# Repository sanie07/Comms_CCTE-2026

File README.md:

# Comms_CCTE-2026
Sistema de comunicación para el cohete suborbital URUTAU-III.

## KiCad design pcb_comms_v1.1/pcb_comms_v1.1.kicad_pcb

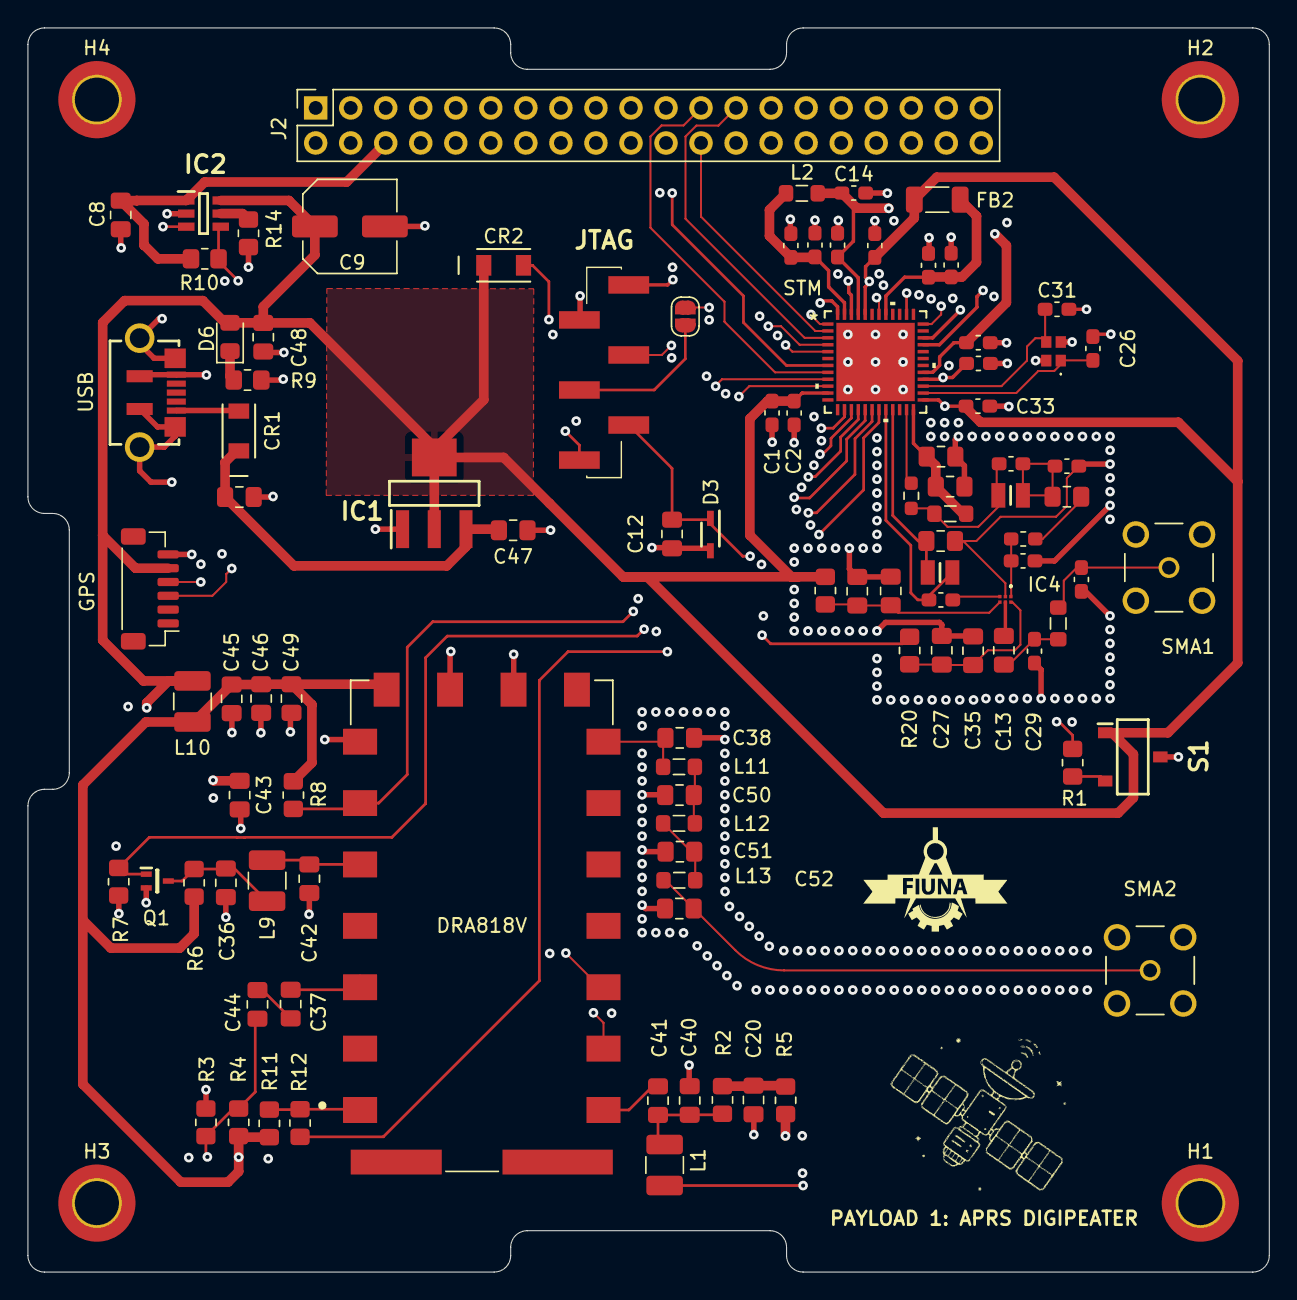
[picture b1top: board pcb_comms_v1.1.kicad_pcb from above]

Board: 4 copper layers, 90.0 x 90.2 mm, 102 parts (0 on the bottom side), 63 nets.

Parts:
C1, C6, C10: 4.7uF; C_0603_1608Metric_Pad1.08x0.95mm_HandSolder
C2, C3, C7, C11, C16: 0.1uF; C_0603_1608Metric_Pad1.08x0.95mm_HandSolder
C8, C39, C46, C49: 10uF; C_0805_2012Metric_Pad1.18x1.45mm_HandSolder
C9: 150uF; C_Elec_6.3x7.7
C12, C43: 0.1uF; C_0805_2012Metric_Pad1.18x1.45mm_HandSolder
C13, C18, C19: 68pF; C_0805_2012Metric_Pad1.18x1.45mm_HandSolder
C14: 0.47uF; C_0603_1608Metric_Pad1.08x0.95mm_HandSolder
C15: 47nF; C_0805_2012Metric_Pad1.18x1.45mm_HandSolder
C17: 2.7pF; C_0603_1608Metric_Pad1.08x0.95mm_HandSolder
C20, C44, C47: 1uF; C_0805_2012Metric_Pad1.18x1.45mm_HandSolder
C21: 15pF; C_0603_1608Metric_Pad1.08x0.95mm_HandSolder
C22: 5.6pF; C_0603_1608Metric_Pad1.08x0.95mm_HandSolder
C23, C27: 10pF; C_0805_2012Metric_Pad1.18x1.45mm_HandSolder
C24: 3.6pF; C_0603_1608Metric_Pad1.08x0.95mm_HandSolder
C25, C35, C36, C42, C45: 1nF; C_0805_2012Metric_Pad1.18x1.45mm_HandSolder
C26, C31: 6.8pF; C_0603_1608Metric_Pad1.08x0.95mm_HandSolder
C28, C29: 8.2pF; C_0603_1608Metric_Pad1.08x0.95mm_HandSolder
C30: 4.3pF; C_0805_2012Metric_Pad1.18x1.45mm_HandSolder
C32, C33, C34: 33pF; C_0603_1608Metric_Pad1.08x0.95mm_HandSolder
C37, C41: 220nF; C_0805_2012Metric_Pad1.18x1.45mm_HandSolder
C38, C52: 20pF; C_0805_2012Metric_Pad1.18x1.45mm_HandSolder
C40: 220pF; C_0805_2012Metric_Pad1.18x1.45mm_HandSolder
C48: 4.7uF; C_0805_2012Metric_Pad1.18x1.45mm_HandSolder
C50, C51: 36pF; C_0805_2012Metric_Pad1.18x1.45mm_HandSolder
CR1, CR2: SD1206S040S1R0; SCHOTTKY_DIODE_SD1206S040S1R0
D3: AQ3530-01FTG; ESD_PROTECTION_DIODE_AQ3530-01FTG
D6: GREEN; LED_0805_2012Metric_Pad1.15x1.40mm_HandSolder
DRA818V: DRA818V; DORJI_DRA818V
FB2: 600R; L_1206_3216Metric_Pad1.22x1.90mm_HandSolder
GPS: CONN_GPS; JST_SH_BM06B-SRSS-TB_1x06-1MP_P1.00mm_Vertical
H1, H2, H3, H4: MountingHole; MountingHole_3.2mm_M3_DIN965_Pad_TopBottom
IC1: LDL1117S33R; LDO_LDL1117S33R
IC2: TPS2553QDBVRQ1; SOT95P280X145-6N
IC4: BGS12WN6E6329XTSA1
J2: Conn_02x20_Odd_Even; PinSocket_2x20_P2.54mm_Vertical
JTAG: Conn_01x06_Pin; CONN_01x06_87898-0666
L1, L9, L10: 1uH; L_1210_3225Metric_Pad1.42x2.65mm_HandSolder
L2: 15uH; L_0805_2012Metric_Pad1.05x1.20mm_HandSolder
L3, L11, L13: 56nH; L_0805_2012Metric_Pad1.05x1.20mm_HandSolder
L4: 12nH; Inductor_0805_2015metric
L5: 20nH; L_0603_1608Metric_Pad1.05x0.95mm_HandSolder
L6: 0R; R_0603_1608Metric_Pad0.98x0.95mm_HandSolder
L7: 18nH; L_0805_2012Metric_Pad1.05x1.20mm_HandSolder
L8: 36nH; Inductor_0805_2015metric
L12: 68nH; L_0805_2012Metric_Pad1.05x1.20mm_HandSolder
Q1: DTC144EET1G; TRANSISTOR_DTC144EET1G
R1, R2, R3, R4, R6, R7, R8, R10, R11: 10K; R_0805_2012Metric_Pad1.20x1.40mm_HandSolder
R5, R9: 1K; R_0805_2012Metric_Pad1.20x1.40mm_HandSolder
R12, R19, R20: 100R; R_0805_2012Metric_Pad1.20x1.40mm_HandSolder
R14: 26.1K; R_0805_2012Metric_Pad1.20x1.40mm_HandSolder
S1: CJS-1200B1; SW_BOOT_CJS-1200B1
SB3: Open; SolderJumper-2_P1.3mm_Open_RoundedPad1.0x1.5mm
SMA1, SMA2: SMA_CONNECTOR; LPRS_SMA_CONNECTOR
STM: STM32WLE5CCU6; UFQFPN48_STM
USB: USB-B-Micro; USB_RECEPTACLE_105164-0001
Y3: 32MHz; STM32WLE5_Crystal_32MHz_ECS320837CKMTR3

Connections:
+3V3: C1.2, C2.2, C3.2, C9.1, C32.1, C33.1, C43.1, C48.1, CR2.1, D6.2 (A), FB2.1, GPS.5, IC1.2 (VOUT_1), IC1.4 (VOUT_2), IC2.6 (OUT), L10.1, R19.2, S1.1, STM.11 (VDD), STM.25 (VDDPA), STM.28 (VDDRF), STM.44 (VDD), STM.46 (VDDSMPS)
+5V: C39.1, C47.1, CR1.1, IC1.3 (VIN)
/APRS_RADIO/3V3_DRA: C45.1, C46.1, C49.1, DRA818V.8 (VBAT), L10.2, R4.2, R5.2, R6.2, R8.2, R11.2
/APRS_RADIO/3V3_DRA1: C20.1, R2.2, R5.1
/APRS_RADIO/AF_OUT: C37.1, DRA818V.3 (AF_OUT)
/APRS_RADIO/AF_OUT2: C37.2, C44.2
/APRS_RADIO/ANT1: C50.1, L11.2, L12.1
/APRS_RADIO/ANT2: C51.1, L12.2, L13.1
/APRS_RADIO/DRA_ANT: C52.1, L13.2, SMA2.1
/APRS_RADIO/DRA_ANT_NO_FILTER: C38.1, DRA818V.12 (ANT), L11.1
/APRS_RADIO/DRA_PTT: C42.1, DRA818V.5 (PTT), L9.2
/APRS_RADIO/DRA_PTT2: C36.1, L9.1, Q1.3 (C), R6.1
/APRS_RADIO/MIC_IN: C41.2, DRA818V.18 (MIC_IN)
/APRS_RADIO/MIC_IN1: C40.1, C41.1, L1.2, R2.1
/IO_CONN/VBUS: CR1.2, USB.1 (VBUS)
/MCU/STM32_BOOT: R1.1, STM.19 (PH3-BOOT0)
/MCU/STM32_OSC_IN: C26.2, STM.26 (OSC_IN), Y3.1 (IN/OUT)
/MCU/STM32_OSC_OUT: C31.2, STM.27 (OSC_OUT), Y3.3 (OUT/IN)
/MCU/VDDA: C6.1, C7.1, FB2.2, STM.41 (VDDA)
/MCU/VDDRF1V55: C14.1, C16.1, C34.1, L2.2, STM.29 (VDDRF1V55), STM.45 (VFBSMPS)
/MCU/VLXSMPS: C10.1, C11.1, L2.1, STM.47 (VLXSMPS)
/OCP/D6_TO_R9: D6.1 (K), R9.2
/OCP/ILIM: IC2.5 (ILIM), R14.1
/RF/RF1: C24.2, IC4.3 (RF1)
/RF/RF2: C22.1, IC4.1 (RF2), L5.2
/RF/RFIN: C13.2, IC4.5 (RFIN)
/RF/RFIN2: C13.1, C29.2, L7.2
/RF/RFO_TO_CAP: C17.1, L3.2, L4.1, L6.2
/RF/RF_C19_TO_L5: C19.2, L5.1
/RF/RF_NODO1: C17.2, C19.1, C21.1, L4.2
/RF/SMA1: C28.2, L7.1, SMA1.1
/RF/SWITCH_TO_CRL: C27.1, C35.1, IC4.6 (CTRL), R20.1
/RF/VDD_SWITCH_RF: C23.1, C25.1, IC4.4 (VDD), R19.1
DRA_RX_UART1_TX: DRA818V.16 (RXD), STM.4 (PB6)
DRA_SQ_TO_STM32: R12.1, STM.16 (PA8)
DRA_TO_STM32_ADC: C44.1, R3.1, R4.1, STM.34 (PA11)
DRA_TX_UART1_RX: DRA818V.17 (TXD), STM.5 (PB7)
GND: C1.1, C2.1, C3.1, C6.2, C7.2, C8.2, C9.2, C10.2, C11.2, C12.2, C14.2, C15.2, C16.2, C18.2, C20.2, C21.2, C22.2, C23.2, C25.2, C26.1, C27.2, C28.1, C29.1, C30.2, C31.1, C32.2, C33.2, C34.2, C35.2, C36.2, C38.2, C39.2, C40.2, C42.2, C43.2, C45.2, C46.2, C47.2, C48.2, C49.2, C50.2, C51.2, C52.2, D3.2 (A), DRA818V.7 (H/L), DRA818V.9 (GND), DRA818V.10 (GND), GPS.6, IC1.1 (GND), IC2.2 (GND), IC4.2 (GND), J2.3, J2.4, J2.7, J2.8, J2.11, J2.12, J2.13, J2.14, J2.17, J2.18, J2.21, J2.22, J2.27, J2.28, J2.36, J2.37, J2.38, J2.39, J2.40, JTAG.2, Q1.2 (E), R3.2, R7.1, R9.1, R14.2, S1.3, SMA1.G1, SMA1.G2, SMA1.G3, SMA1.G4, SMA2.G1, SMA2.G2, SMA2.G3, SMA2.G4, STM.48 (VSSSMPS), STM.49 (GND), USB.5 (GND), USB.MH1, USB.MH2, USB.MP1, USB.MP2, USB.MP3, USB.MP4, Y3.2 (GND_1), Y3.4 (GND_2)
JTCK_SWCLK_TO_STM32: JTAG.3, STM.42 (PA14)
JTDO_SWO_TO_STM32: SB3.2 (B), STM.1 (PB3)
JTMS_SWDIO_TO_STM32: JTAG.1, STM.36 (PA13)
unnamed: JTAG.4, SB3.1 (A)
unnamed: CR2.2, JTAG.6
unnamed: R1.2, S1.2 (C)
unnamed: DRA818V.1 (SQ), R11.1, R12.2
OCP_EN: IC2.3 (EN), J2.29
OCP_NFAULT: IC2.4 (FAULT), R10.2, STM.38 (PC13)
RFI_N: C30.1, L8.2, STM.21 (RFI_N)
RFI_P: C24.1, L8.1, STM.20 (RFI_P)
RFO_HP: L6.1, STM.23 (RFO_HP)
RF_CRL_TO_STM32: R20.2, STM.17 (PA9)
SPI1_CS: J2.26, STM.7 (PA0)
SPI1_MISO: J2.24, STM.2 (PB4)
SPI1_MOSI: J2.25, STM.3 (PB5)
SPI1_SCK: J2.23, STM.8 (PA1)
STM32_DAC_TO_DRA: L1.1, STM.33 (PA10)
STM32_NRST: C12.1, D3.1 (K), JTAG.5, STM.18 (NRST)
STM32_TO_DRA_ENA: DRA818V.6 (PD), R8.1, STM.14 (PA6)
STM32_TO_DRA_PTT: Q1.1 (B), R7.2, STM.15 (PA7)
UART2_TX: GPS.3, STM.9 (PA2)
UART_RX: GPS.4, STM.10 (PA3)
VBAT_IN: C8.1, IC2.1 (IN), J2.5, J2.6, R10.1
VR_PA: C15.1, C18.1, L3.1, STM.24 (VR_PA)

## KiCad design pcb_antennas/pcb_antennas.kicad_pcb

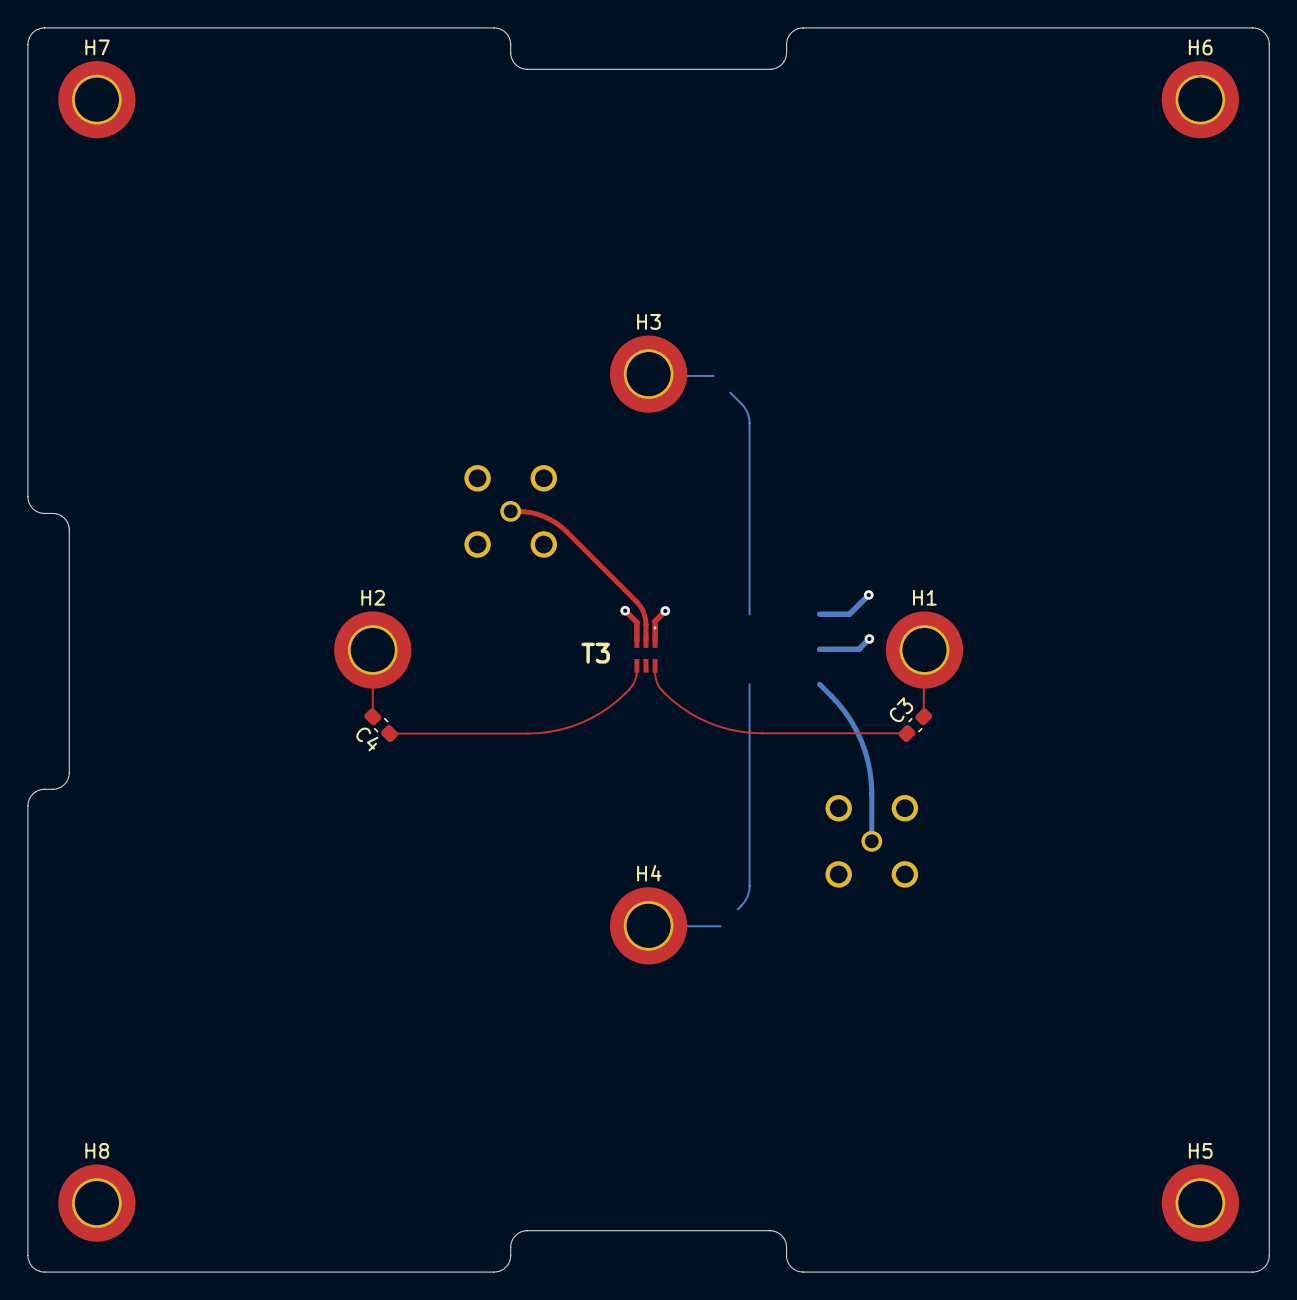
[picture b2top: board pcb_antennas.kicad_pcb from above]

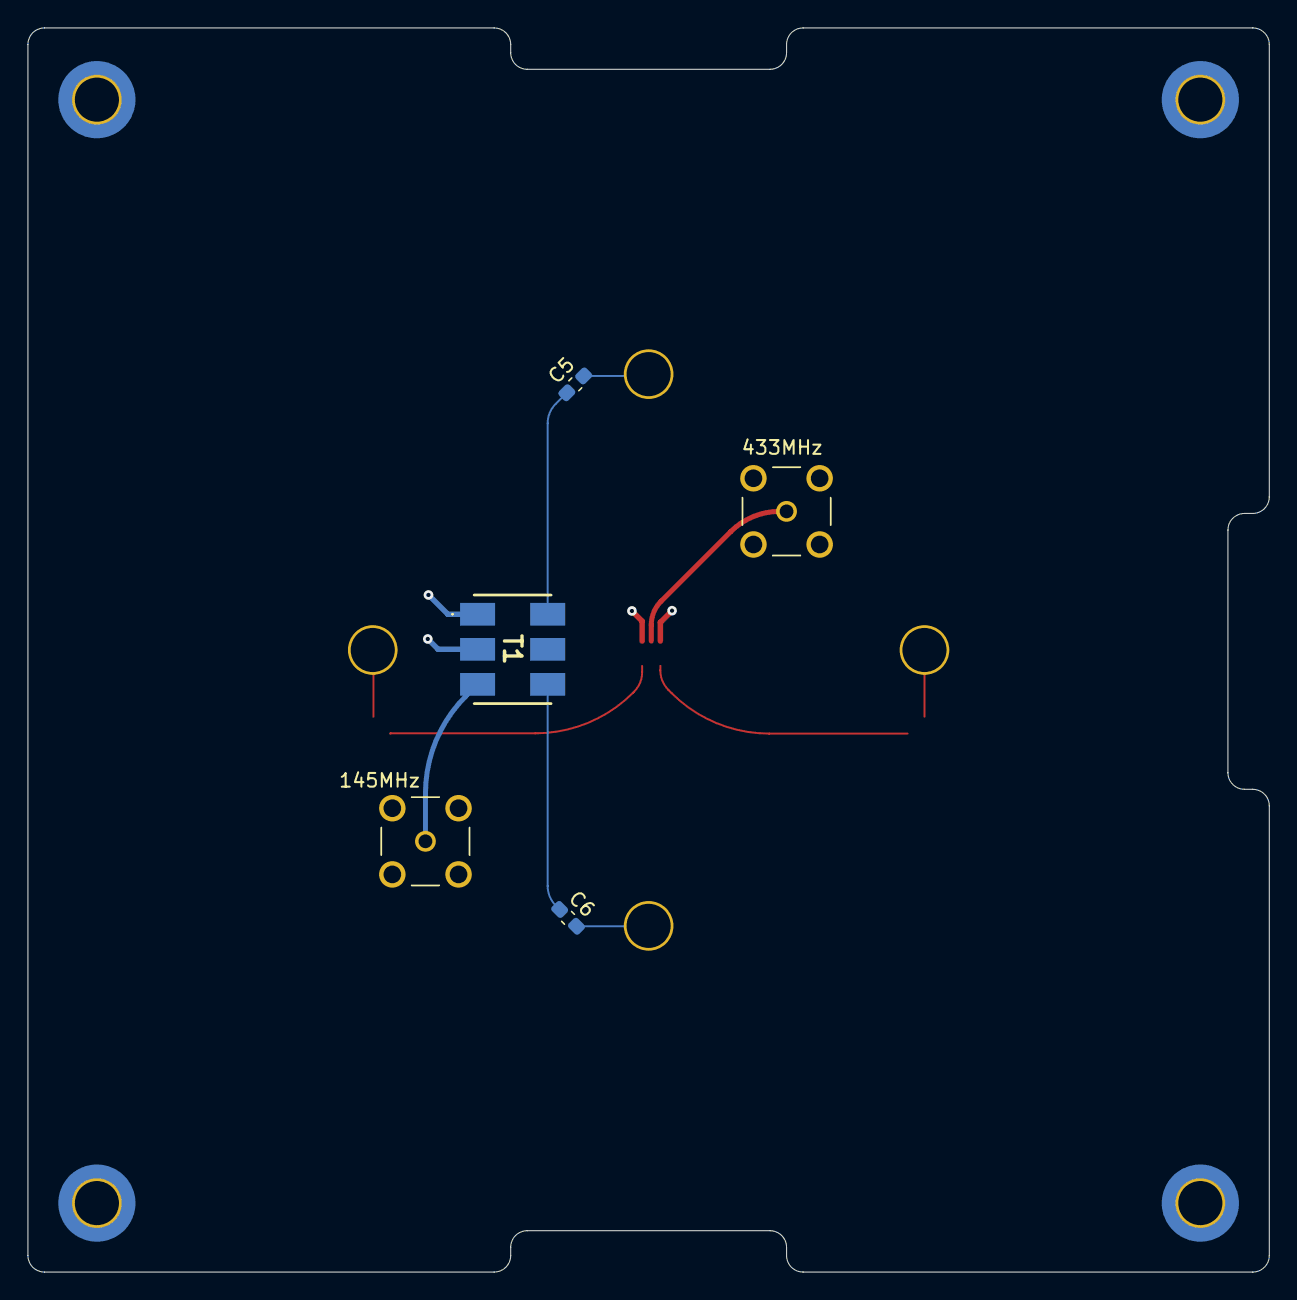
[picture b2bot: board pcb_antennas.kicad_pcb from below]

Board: 4 copper layers, 90.0 x 90.2 mm, 16 parts (5 on the bottom side), 11 nets.

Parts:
145MHz, 433MHz: SMA_CONNECTOR; LPRS_SMA_CONNECTOR
C3, C4: 47pF; C_0603_1608Metric_Pad1.08x0.95mm_HandSolder
C5, C6: 150pF; C_0603_1608Metric_Pad1.08x0.95mm_HandSolder
H1, H2, H3, H4: MountingHole_Pad; MountingHole_3.2mm_M3_DIN965_Pad_TopOnly
H5, H6, H7, H8: MountingHole; MountingHole_3.2mm_M3_DIN965_Pad_TopBottom
T1: ADT1.5-122+; ADT15122
T3: NCS1.5-232+; NCS15232

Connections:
/SMA_145: 145MHz.1, T1.3 (PRIMARY_DOT_50ohm_UNBALANCED)
/SMA_433: 433MHz.1, T3.2 (PRIMARY_DOT_(UNBALANCED_PORT))
/SeAc21_75ohms: C5.2, H3.1
/Sec1_75ohms: C3.1, T3.6 (SECONDARY_(BALANCED))
/Sec2_75ohms: C4.1, T3.4 (SECONDARY_DOT_(BALANCED))
/Sec12_75ohms: C3.2, H1.1
/Sec22_75ohms: C4.2, H2.1
/SecA1_75ohms: C5.1, T1.6 (SECONDARY_75ohm_BALANCED)
/SecA2_75ohms: C6.1, T1.4 (SECONDARY_DOT_75ohm_BALANCED)
/SecA22_75ohms: C6.2, H4.1
GND: 145MHz.G1, 145MHz.G2, 145MHz.G3, 145MHz.G4, 433MHz.G1, 433MHz.G2, 433MHz.G3, 433MHz.G4, T1.1 (PRIMARY_1), T1.2 (PRIMARY_2), T3.1 (PRIMARY_(GND)_1), T3.3 (PRIMARY_(GND)_2)

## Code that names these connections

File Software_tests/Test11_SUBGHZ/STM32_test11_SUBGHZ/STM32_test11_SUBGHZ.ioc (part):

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Mcu.Name=STM32WLE5CCUx
Mcu.Package=UFQFPN48
Mcu.UserName=STM32WLE5CCUx
PA0.GPIOParameters=GPIO_Label,GPIO_ModeDefaultEXTI
PA0.GPIO_Label=SPI1_CS
PA0.GPIO_ModeDefaultEXTI=GPIO_MODE_IT_RISING_FALLING
PA0.Signal=GPXTI0
PA1.Mode=Full_Duplex_Slave
PA1.Signal=SPI1_SCK
PA10.GPIOParameters=GPIO_Label
PA10.GPIO_Label=STM32_DAC_TO_DRA
PA10.Signal=COMP_DAC1_group
PA11.GPIOParameters=GPIO_Label
PA11.GPIO_Label=DRA_TO_STM32_ADC
PA11.Mode=IN7
PA11.Signal=ADC_IN7
PA13.Mode=Trace_Asynchronous_SW
PA13.Signal=DEBUG_JTMS-SWDIO
PA14.Mode=Trace_Asynchronous_SW
PA14.Signal=DEBUG_JTCK-SWCLK
PA2.Mode=Asynchronous
PA2.Signal=USART2_TX
PA3.Mode=Asynchronous
PA3.Signal=USART2_RX
PA6.GPIOParameters=GPIO_Label
PA6.GPIO_Label=STM32_TO_DRA_ENA
PA6.Signal=GPIO_Output
PA7.GPIOParameters=GPIO_Label
PA7.GPIO_Label=STM32_TO_DRA_PTT
PA7.Signal=GPIO_Output
PA8.GPIOParameters=GPIO_Label
PA8.GPIO_Label=DRA_SQ_TO_STM32
PA8.Signal=GPIO_Input
PA9.GPIOParameters=GPIO_Label
PA9.GPIO_Label=RF_CRL
PA9.Signal=GPIO_Output
PB3.Mode=Trace_Asynchronous_SW
PB3.Signal=DEBUG_JTDO-SWO
PB4.Mode=Full_Duplex_Slave
PB4.Signal=SPI1_MISO
PB5.Mode=Full_Duplex_Slave
PB5.Signal=SPI1_MOSI
PB6.Mode=Asynchronous
PB6.Signal=USART1_TX
PB7.Mode=Asynchronous
PB7.Signal=USART1_RX
RCC.HSE_VALUE=32000000
RCC.SYSCLKFreq_VALUE=48000000
RCC.SYSCLKSource=RCC_SYSCLKSOURCE_PLLCLK
board=custom

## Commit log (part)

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2026-03-15 Setup project
2026-03-19 Add usb and gps
2026-03-20 Add external circuit for gps
2026-03-30 Update GPS to pasive antenna
2026-04-02 Update GPS
2026-04-02 Add antenna deploy
2026-04-02 Update USB
2026-04-02 Last update
2026-04-04 Update STM cube
2026-04-04 rev 1.1
2026-04-16 Finish schematic
2026-04-18 Version 1.0. No DRA yet
    From now on I will make the connections for IIS and then adapt it for the club
2026-04-20 Add footprints
2026-04-22 Add DRA818
2026-04-23 remove gps
2026-04-25 Update DRA
2026-04-25 Add UART USB
2026-04-25 Update pinout
2026-04-25 Update pinout 2
2026-04-26 Update schematic. Add net classes and JST footprints for aux
2026-04-26 Update pcb
2026-04-27 Route pcb
2026-04-28 Update route
2026-04-29 Version 1.1
2026-04-29 Update schematic
2026-04-29 re arrange
2026-04-29 PCB v2
2026-04-30 PCB v2.1
2026-05-01 PCB v2.2
2026-06-15 Add STM32 gps test 1
2026-06-16 Add esp test code
2026-06-17 Blinking test
    Funciona con el cristal interno
2026-06-21 GPS test
2026-06-24 Test gps with HSE
